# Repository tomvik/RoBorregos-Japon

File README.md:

# RoBorregos-Japon
This repository contains the approach used by RoBorregos Team in the RoboCup 2017 tournament.

RoBorregos is the international representative robotics team of Tecnologico de Monterrey, Campus Monterrey.

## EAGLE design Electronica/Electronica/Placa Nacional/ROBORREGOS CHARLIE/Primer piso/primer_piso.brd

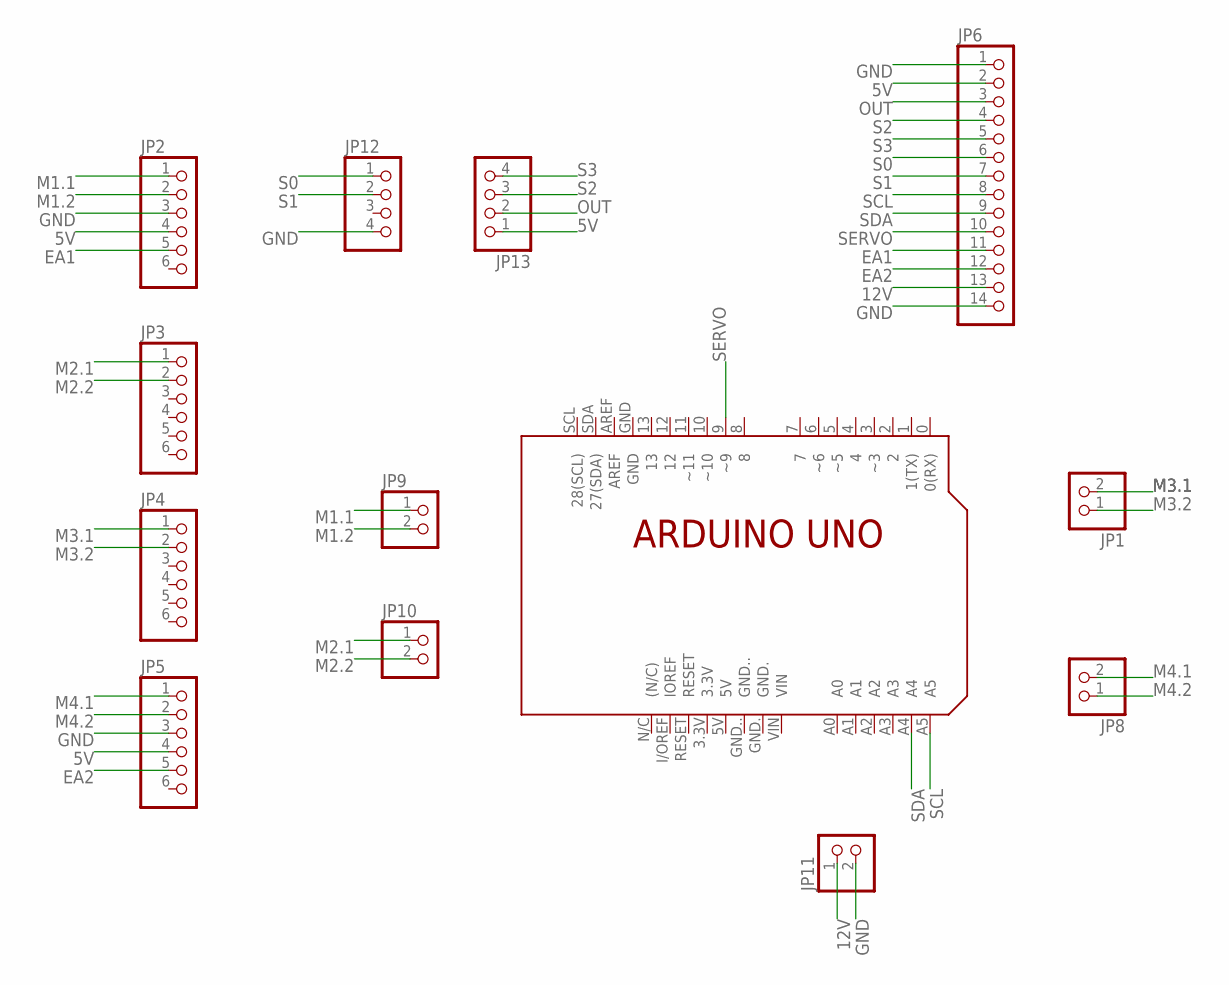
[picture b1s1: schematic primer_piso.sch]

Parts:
JP1, JP8, JP9, JP10, JP11: PINHD-1X2; 1X02
JP2, JP3, JP4, JP5: PINHD-1X6; 1X06
JP6: PINHD-1X14; 1X14
JP12, JP13: PINHD-1X4; 1X04
UNO1: UNO

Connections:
5V: JP2.4, JP5.4, JP6.2, JP13.1
12V: JP6.13, JP11.1
EA1: JP2.5, JP6.11
EA2: JP5.5, JP6.12
GND: JP2.3, JP5.3, JP6.1, JP6.14, JP11.2, JP12.4
M1.1: JP2.1, JP9.1
M1.2: JP2.2, JP9.2
M2.1: JP3.1, JP10.1
M2.2: JP3.2, JP10.2
M3.1: JP1.2, JP4.1
M3.2: JP1.1, JP4.2
M4.1: JP5.1, JP8.2
M4.2: JP5.2, JP8.1
OUT: JP6.3, JP13.2
S0: JP6.6, JP12.1
S1: JP6.7, JP12.2
S2: JP6.4, JP13.3
S3: JP6.5, JP13.4
SCL: JP6.8, UNO1.A5
SDA: JP6.9, UNO1.A4
SERVO: JP6.10, UNO1.9 (~9)

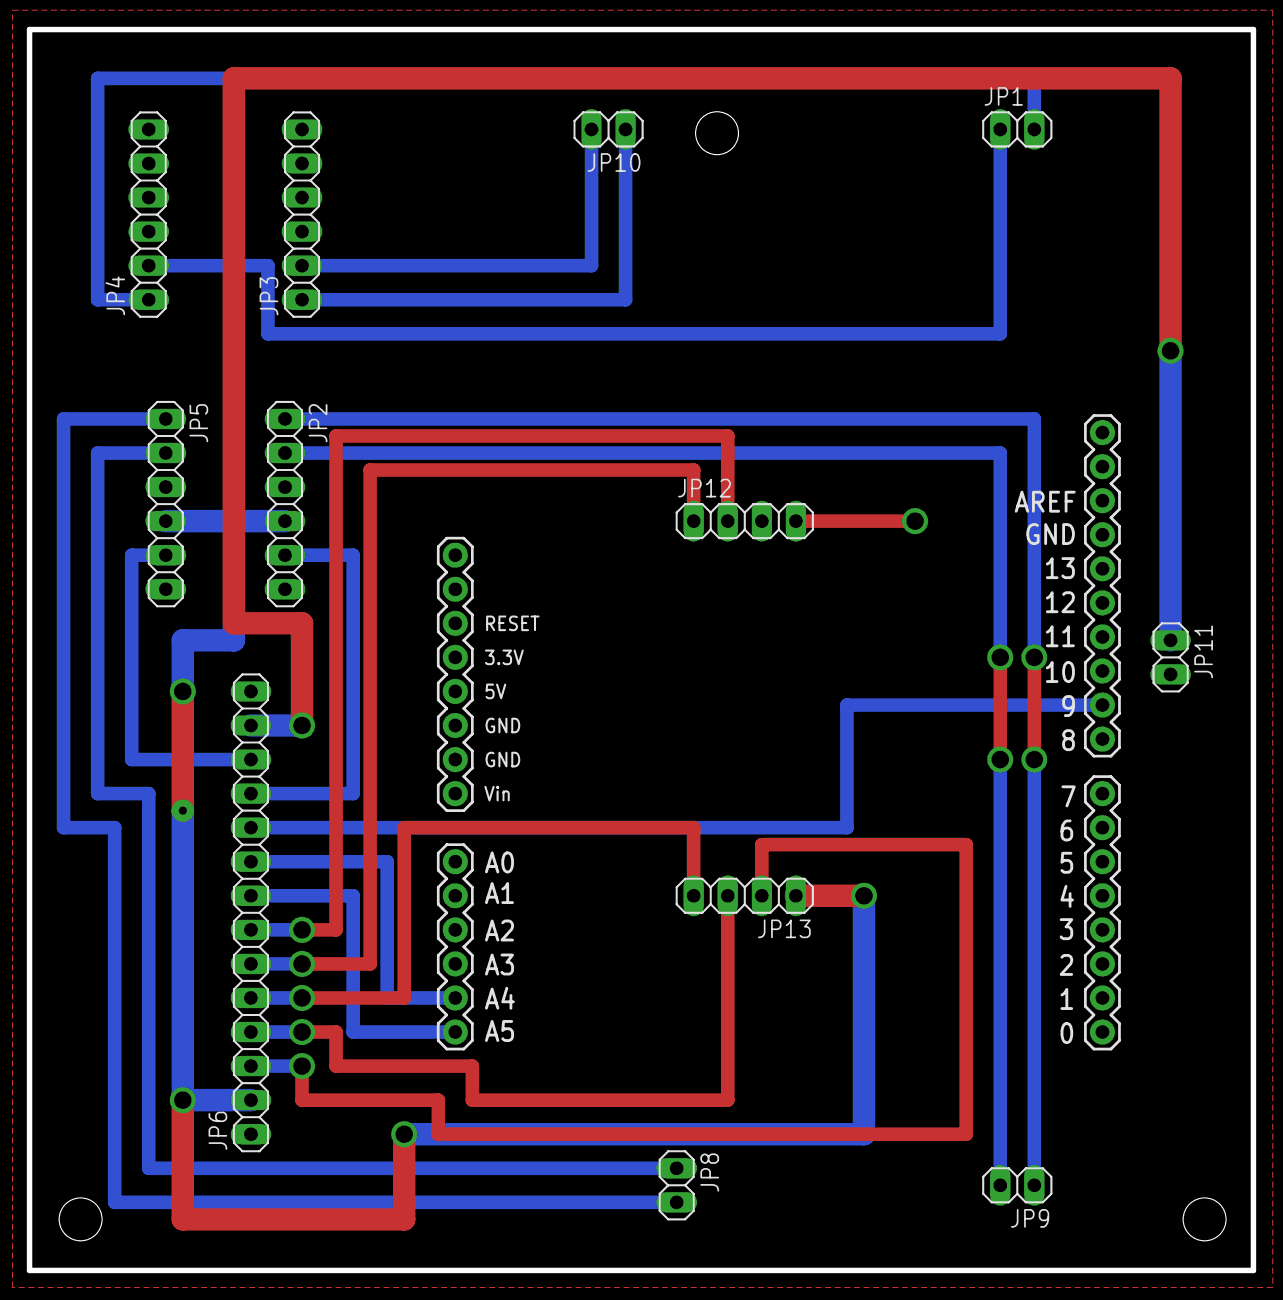
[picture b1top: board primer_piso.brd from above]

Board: 2 copper layers, 91.3 x 92.5 mm, 13 parts (0 on the bottom side), 21 nets.

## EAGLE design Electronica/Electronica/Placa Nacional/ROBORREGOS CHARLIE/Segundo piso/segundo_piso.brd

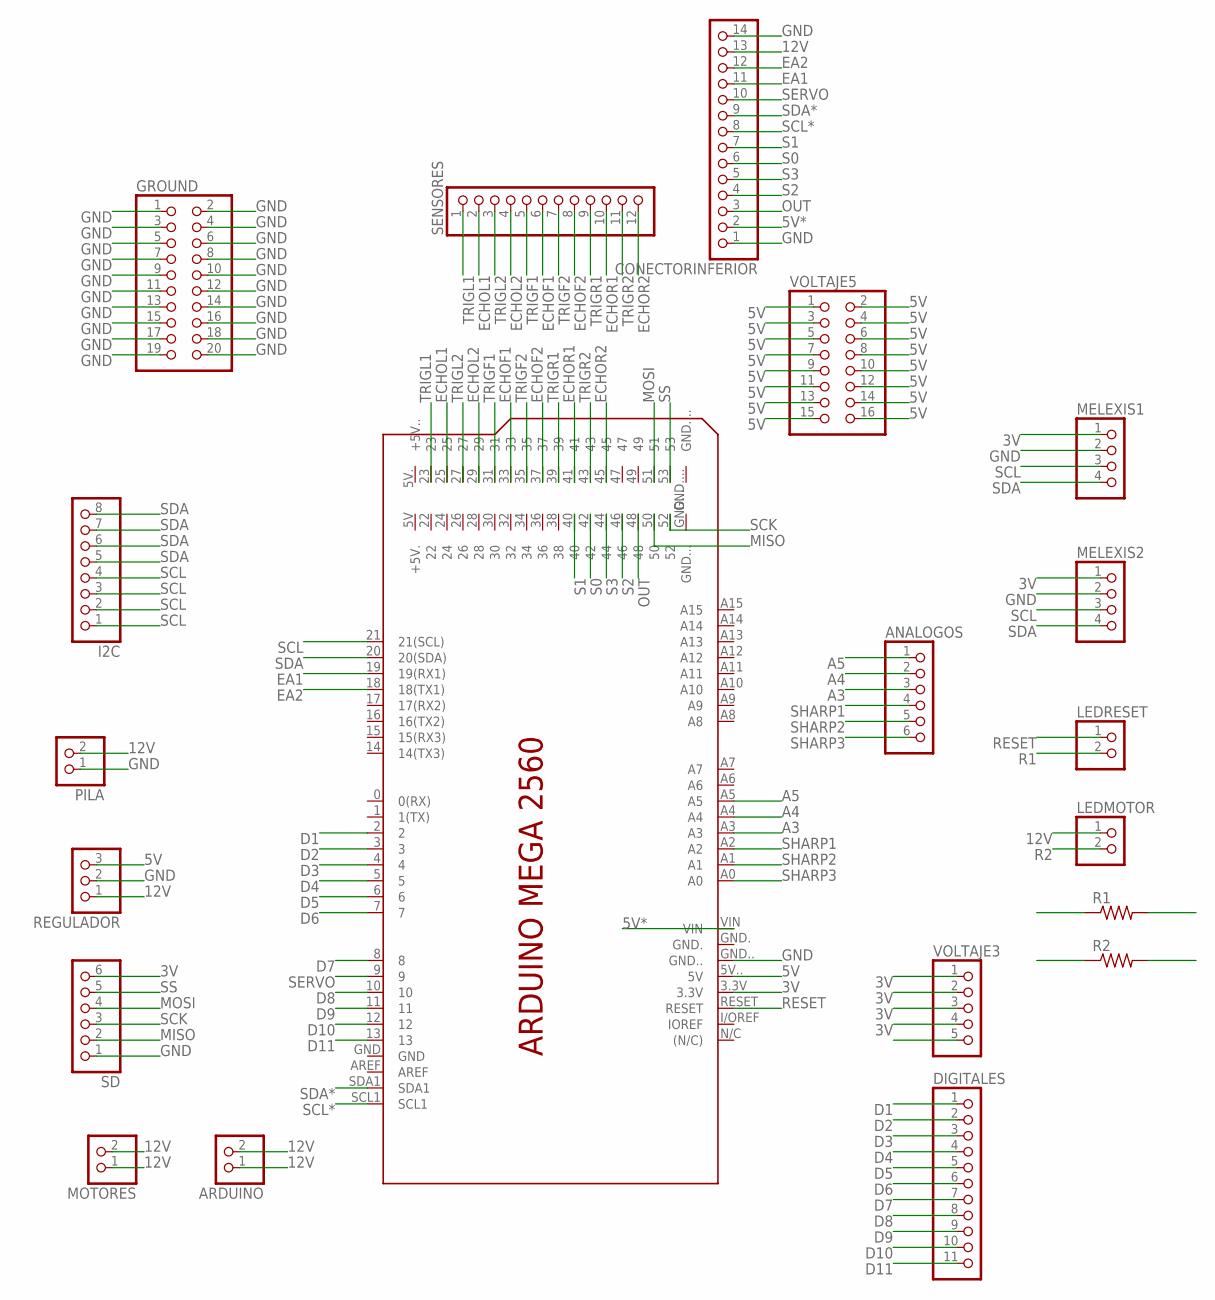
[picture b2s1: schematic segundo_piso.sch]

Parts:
ANALOGOS: PINHD-1X6; 1X06
ARDUINO: PINHD-1X2; 1X02
CONECTORINFERIOR: PINHD-1X14; 1X14
DIGITALES: PINHD-1X11; 1X11
GROUND: PINHD-2X10; 2X10
I2C: PINHD-1X8; 1X08
LEDMOTOR: PINHD-1X2; 1X02
LEDRESET: PINHD-1X2; 1X02
MEGA1: MEGA
MELEXIS1, MELEXIS2: PINHD-1X4; 1X04
MOTORES: PINHD-1X2; 1X02
PILA: PINHD-1X2; 1X02
R1, R2: R-US_0204/7; 0204/7
REGULADOR: PINHD-1X3; 1X03
SD: PINHD-1X6; 1X06
SENSORES: PINHD-1X12; 1X12
VOLTAJE3: PINHD-1X5; 1X05
VOLTAJE5: PINHD-2X8; 2X08

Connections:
3V: MEGA1.3.3V, MELEXIS1.1, MELEXIS2.1, SD.6, VOLTAJE3.1, VOLTAJE3.2, VOLTAJE3.3, VOLTAJE3.4
5V: MEGA1.5V.. (5V), REGULADOR.3, VOLTAJE5.1, VOLTAJE5.2, VOLTAJE5.3, VOLTAJE5.4, VOLTAJE5.5, VOLTAJE5.6, VOLTAJE5.7, VOLTAJE5.8, VOLTAJE5.9, VOLTAJE5.10, VOLTAJE5.11, VOLTAJE5.12, VOLTAJE5.13, VOLTAJE5.14, VOLTAJE5.15, VOLTAJE5.16
5V*: CONECTORINFERIOR.2, MEGA1.VIN
12V: ARDUINO.1, ARDUINO.2, CONECTORINFERIOR.13, LEDMOTOR.1, MOTORES.1, MOTORES.2, PILA.2, REGULADOR.1
A3: ANALOGOS.3, MEGA1.A3
A4: ANALOGOS.2, MEGA1.A4
A5: ANALOGOS.1, MEGA1.A5
D1: DIGITALES.1, MEGA1.2
D2: DIGITALES.2, MEGA1.3
D3: DIGITALES.3, MEGA1.4
D4: DIGITALES.4, MEGA1.5
D5: DIGITALES.5, MEGA1.6
D6: DIGITALES.6, MEGA1.7
D7: DIGITALES.7, MEGA1.8
D8: DIGITALES.8, MEGA1.10
D9: DIGITALES.9, MEGA1.11
D10: DIGITALES.10, MEGA1.12
D11: DIGITALES.11, MEGA1.13
EA1: CONECTORINFERIOR.11, MEGA1.19 (19(RX1))
EA2: CONECTORINFERIOR.12, MEGA1.18 (18(TX1))
ECHOF1: MEGA1.33, SENSORES.6
ECHOF2: MEGA1.37, SENSORES.8
ECHOL1: MEGA1.25, SENSORES.2
ECHOL2: MEGA1.29, SENSORES.4
ECHOR1: MEGA1.41, SENSORES.10
ECHOR2: MEGA1.45, SENSORES.12
GND: CONECTORINFERIOR.1, CONECTORINFERIOR.14, GROUND.1, GROUND.2, GROUND.3, GROUND.4, GROUND.5, GROUND.6, GROUND.7, GROUND.8, GROUND.9, GROUND.10, GROUND.11, GROUND.12, GROUND.13, GROUND.14, GROUND.15, GROUND.16, GROUND.17, GROUND.18, GROUND.19, GROUND.20, MEGA1.GND.., MELEXIS1.2, MELEXIS2.2, PILA.1, R1.2, R2.2, REGULADOR.2, SD.1
MISO: MEGA1.50, SD.2
MOSI: MEGA1.51, SD.4
OUT: CONECTORINFERIOR.3, MEGA1.48
R1: LEDRESET.2, R1.1
R2: LEDMOTOR.2, R2.1
RESET: LEDRESET.1, MEGA1.RESET, VOLTAJE3.5
S0: CONECTORINFERIOR.6, MEGA1.42
S1: CONECTORINFERIOR.7, MEGA1.40
S2: CONECTORINFERIOR.4, MEGA1.46
S3: CONECTORINFERIOR.5, MEGA1.44
SCK: MEGA1.52, SD.3
SCL: I2C.1, I2C.2, I2C.3, I2C.4, MEGA1.21 (21(SCL)), MELEXIS1.3, MELEXIS2.3
SCL*: CONECTORINFERIOR.8, MEGA1.SCL1
SDA: I2C.5, I2C.6, I2C.7, I2C.8, MEGA1.20 (20(SDA)), MELEXIS1.4, MELEXIS2.4
SDA*: CONECTORINFERIOR.9, MEGA1.SDA1
SERVO: CONECTORINFERIOR.10, MEGA1.9
SHARP1: ANALOGOS.4, MEGA1.A2
SHARP2: ANALOGOS.5, MEGA1.A1
SHARP3: ANALOGOS.6, MEGA1.A0
SS: MEGA1.53, SD.5
TRIGF1: MEGA1.31, SENSORES.5
TRIGF2: MEGA1.35, SENSORES.7
TRIGL1: MEGA1.23, SENSORES.1
TRIGL2: MEGA1.27, SENSORES.3
TRIGR1: MEGA1.39, SENSORES.9
TRIGR2: MEGA1.43, SENSORES.11

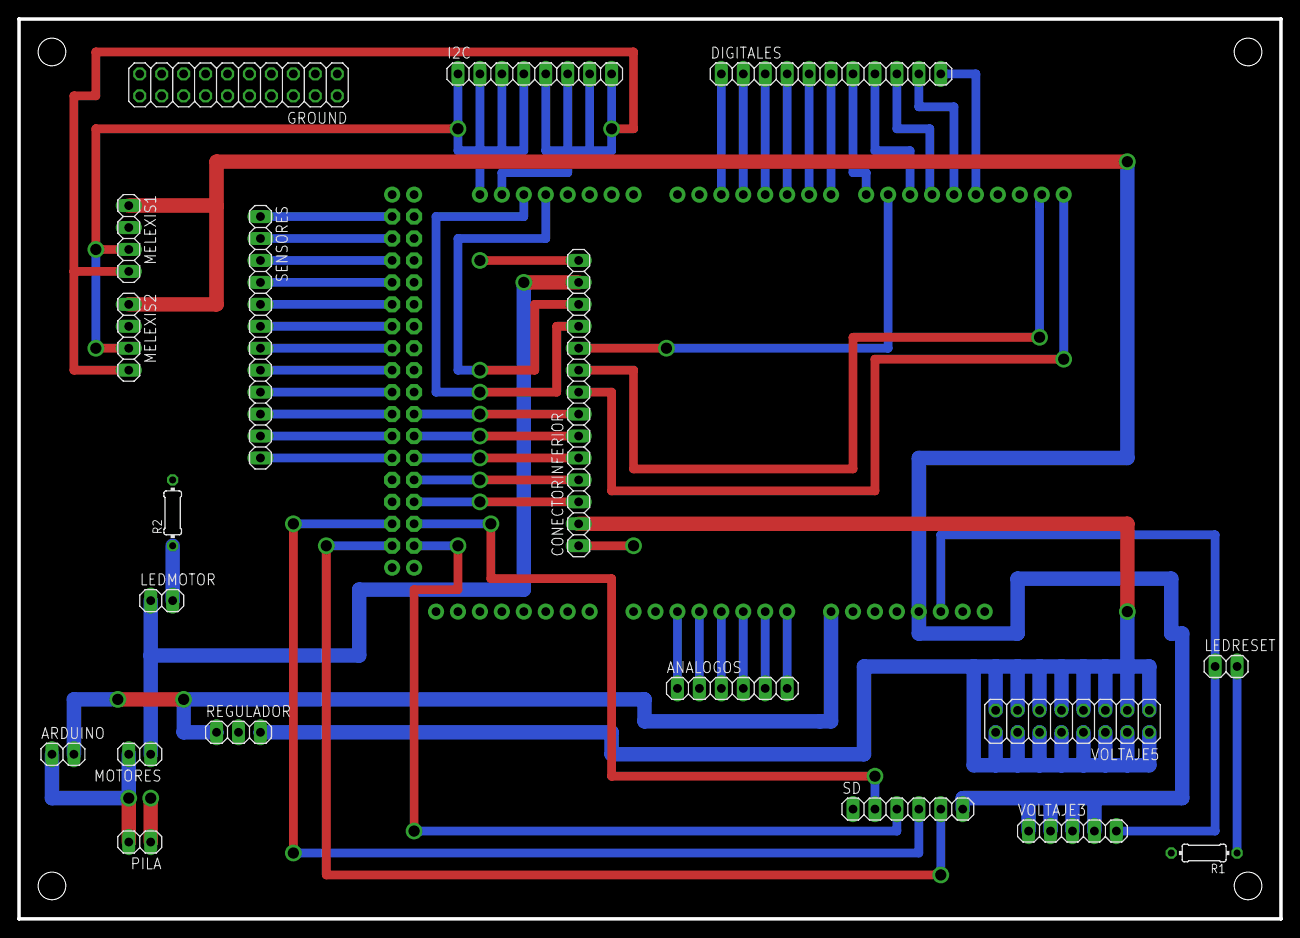
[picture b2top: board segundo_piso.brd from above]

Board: 2 copper layers, 146.1 x 104.1 mm, 20 parts (1 on the bottom side), 53 nets.

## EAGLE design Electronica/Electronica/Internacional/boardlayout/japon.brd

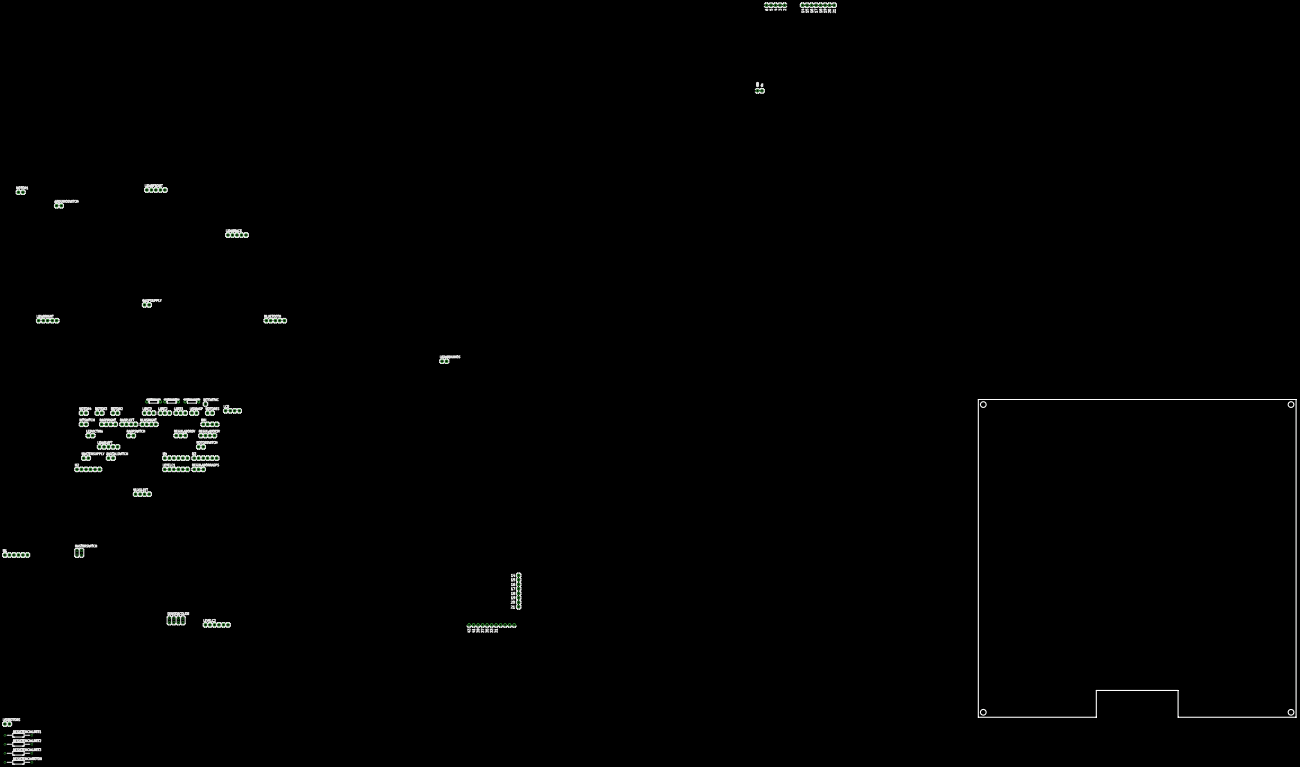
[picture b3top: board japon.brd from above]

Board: 2 copper layers, 179.1 x 179.1 mm, 51 parts (0 on the bottom side), 61 nets, no tracks yet.

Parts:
ARDUINOSWITCH: 1X02
BLUETOOTH: 1X05
DIGITALSWITCH: 1X02
IMU: 1X04
INTSWITCH: 1X02
INTSWITHC: 1X01
LCD: 1X04
LEDARDUINOS: 1X02
LEDMOTORS: 1X02
LEDRASP: 1X02
LEDVICTIMA: 1X02
LEVELC1, LEVELC2: 1X06
LIDARBACK: 1X05
LIDARFRONT: 1X05
LIDARLEFT: 1X05
LIDARRIGHT: 1X05
LIMIT1, LIMIT2, LIMIT3: 1X03
M1, M2, M3, M4: 1X06
MASTERSUPPLY: 1X02
MASTERSWITCH: 2X02
MLXSLEFT: 1X04
MLXSRIGHT: 1X04
MOTOR1, MOTOR2, MOTOR3, MOTOR4: 1X02
MOTORES: 1X02
MOTORSWITCH: 1X02
RASPLEFT: 1X04
RASPRIGHT: 1X04
RASPSUPPLY: 1X02
RASPSWITCH: 1X02
REGULADOR3V: 1X04
REGULADOR5V: 1X03
REGULADORRASPS: 1X03
RESISTENCIAARDUINOS: 1M; AXIAL-0.3
RESISTENCIALIMIT1, RESISTENCIALIMIT2, RESISTENCIALIMIT3: 0207/15
RESISTENCIAMOTOR: 0207/15
RESISTENCIARASPS: 1M; AXIAL-0.3
RESISTENCIAVICTIMAS: 1M; AXIAL-0.3
SENSORCOLOR: 2X04
U$1: MEGASLAVE
U$2: MEGAMASTER

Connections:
3V: IMU.4, LEVELC1.3, LIDARBACK.1, LIDARFRONT.1, LIDARLEFT.1, LIDARRIGHT.1, MLXSLEFT.1, MLXSRIGHT.1, REGULADOR3V.3
5V: DIGITALSWITCH.1, INTSWITCH.1, LCD.1, LEVELC2.4, LIMIT1.3, LIMIT2.3, LIMIT3.3, M1.4, M2.4, REGULADOR5V.3, SENSORCOLOR.8
12V: MASTERSUPPLY.1, MASTERSWITCH.1
12V~: MASTERSWITCH.3, RASPSUPPLY.1
12V~~: ARDUINOSWITCH.1, MASTERSWITCH.2, MOTORSWITCH.1
12V~~~: MASTERSWITCH.4, RASPSWITCH.1
BT: BLUETOOTH.2, U$2.43
DIGSW: DIGITALSWITCH.2, U$2.23
ENCODER1: M1.5, U$2.19
ENCODER2: M2.5, U$2.18
GND: BLUETOOTH.3, IMU.3, LCD.2, LEVELC1.4, LEVELC2.3, LIDARBACK.2, LIDARFRONT.2, LIDARLEFT.2, LIDARRIGHT.2, M1.3, M2.3, M3.3, M4.3, MASTERSUPPLY.2, MLXSLEFT.2, MLXSRIGHT.2, MOTORES.2, RASPLEFT.3, RASPRIGHT.3, RASPSUPPLY.2, REGULADOR3V.2, REGULADOR3V.4, REGULADOR5V.2, REGULADORRASPS.2, RESISTENCIAARDUINOS.P$2, RESISTENCIALIMIT1.2, RESISTENCIALIMIT2.2, RESISTENCIALIMIT3.2, RESISTENCIAMOTOR.2, RESISTENCIARASPS.P$2, RESISTENCIAVICTIMAS.P$2, SENSORCOLOR.7, U$1.GND.
INTSW: INTSWITCH.2, INTSWITHC.1
KEY: BLUETOOTH.1, U$2.41
LIMIT1: LIMIT1.1, U$2.33
LIMIT2: LIMIT2.1, U$2.35
LIMIT3: LIMIT3.1, U$2.37
M1.1: M1.1, MOTOR1.1
M1.2: M1.2, MOTOR1.2
M2.1: M2.1, MOTOR2.1
M2.2: M2.2, MOTOR2.2
M3.1: M3.1, MOTOR3.1
M3.2: M3.2, MOTOR3.2
M4.1: M4.1, MOTOR4.1
M4.2: M4.2, MOTOR4.2
MAIN12: ARDUINOSWITCH.2, LEDARDUINOS.1, REGULADOR3V.1, REGULADOR5V.1, U$1.VIN
MOTOR12: LEDMOTORS.1, MOTORES.1, MOTORSWITCH.2
OUT: SENSORCOLOR.6, U$1.2
R1: LEDARDUINOS.2, RESISTENCIAARDUINOS.P$1
R2: LEDRASP.2, RESISTENCIARASPS.P$1
R3: LEDVICTIMA.2, RESISTENCIAVICTIMAS.P$1
R4: LEDMOTORS.2, RESISTENCIAMOTOR.1
R5: LIMIT1.2, RESISTENCIALIMIT1.1
R6: LIMIT2.2, RESISTENCIALIMIT2.1
R7: LIMIT3.2, RESISTENCIALIMIT3.1
RASPS5: LEDRASP.1, RASPLEFT.4, RASPRIGHT.4, REGULADORRASPS.3
RASPS12: RASPSWITCH.2, REGULADORRASPS.1
RX: U$1.15, U$2.17
RX0: LEVELC2.2, U$1.19
RX0PI: LEVELC1.6, RASPLEFT.2
RX1: LEVELC2.5, U$1.17
RX1PI: LEVELC1.1, RASPRIGHT.2
RX2: BLUETOOTH.4, U$2.15
S0: SENSORCOLOR.1, U$1.3
S1: SENSORCOLOR.3, U$1.4
S2: SENSORCOLOR.4, U$1.5
S3: SENSORCOLOR.2, U$1.6
SCL: IMU.2, LCD.3, LIDARBACK.4, LIDARFRONT.4, LIDARLEFT.4, LIDARRIGHT.4, U$2.21
SCL~: MLXSLEFT.3, MLXSRIGHT.3, U$1.21
SDA: IMU.1, LCD.4, LIDARBACK.3, LIDARFRONT.3, LIDARLEFT.3, LIDARRIGHT.3, U$2.20
SDA~: MLXSLEFT.4, MLXSRIGHT.4, U$1.20
TX: U$1.14, U$2.16
TX0: LEVELC2.1, U$1.18
TX0PI: LEVELC1.5, RASPLEFT.1
TX1: LEVELC2.6, U$1.16
TX1PI: LEVELC1.2, RASPRIGHT.1
TX2: BLUETOOTH.5, U$2.14
VICTIMA: LEDVICTIMA.1, U$2.39
XSHUT1: LIDARFRONT.5, U$2.25
XSHUT2: LIDARRIGHT.5, U$2.27
XSHUT3: LIDARLEFT.5, U$2.29
XSHUT4: LIDARBACK.5, U$2.31

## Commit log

2017-04-24 'Test'
2017-04-29 Rename sketch_nov30a.ino to Algoritmo_Vector1.ino
2017-04-29 Cleans Repository
2017-05-10 Change LibraryCrystal
2017-05-13 Cleaning of functions parameters
2017-05-18 Saves Bumper
2017-05-19 Improvement Go To. Weigthed
2017-05-19 New Control Branch
2017-05-19 Improves Go to function
2017-05-21 Cambios
2017-05-22 Test branch
2017-05-22 Improvement in Path Finding, time and bumper
2017-05-23 Correction of go to error
2017-05-23 Bumper y otras
2017-05-23 Go to final
2017-05-24 LCD everywhere
2017-05-29 Adds puto file
2017-05-30 Tes VL53L0X
2017-06-02 Test VL53L0X
2017-06-02 Improves amount of victims per tile
2017-06-02 Control
2017-06-03 Cleanse Victims
2017-06-04 Improves victim detection
2017-06-04 Limits time Victim
2017-06-05 Cleanse code
2017-06-05 Serial victims
2017-06-05 Improves Serial/Victims/Proccess
2017-06-06 Revert multiple victims
2017-06-06 International mega
2017-06-06 Configurado
2017-06-06 Only one victim/Serial
2017-06-06 Sincronization everything
2017-06-06 Primera
2017-06-06 Folders
2017-06-07 Cambios recientes
2017-06-07 Corrects forward motion
2017-06-14 Nuevo
2017-06-15 Atom
2017-06-17 Versión nueva
2017-06-17 Con ceros
2017-06-17 Ojala
2017-06-18 Limpieza de código y nuevos tests
2017-06-18 Correción en Mapear
2017-06-21 Nuevos test cases, limpieza y cambios de control
2017-06-22 Arreglo en librerias
2017-06-22 Encoder test
2017-06-22 Nuevos test cases y control
2017-06-23 Rename test y IMU
2017-06-23 Version de prueba. CUIDADO.
2017-06-24 IMU changes
2017-06-24 No jala
2017-06-24 Comentar en movimiento
2017-06-24 Revert to f4135be5b3ff2d54e4c8ed66df1c77a3d362dc3d
2017-06-26 Reenommrar
2017-06-26 Nuevos nombres
2017-06-26 Nuevos folders
2017-06-26 Version sin comentar
2017-06-26 Failed
2017-06-27 Encoders, IMU, tests cases, sintaxis
2017-06-28 Sintaxis, control, P e I, vueltas, velocidad, encoder
2017-06-28 Limpieza
2017-06-28 Correciones librerias
2017-06-28 Linrerias
2017-06-28 sintaxis
2017-06-28 Limpieza librerias
2017-06-28 Sintaxis y correciones
2017-06-28 Distancia en milimetros
2017-06-30 Merge
2017-07-01 Correciones y un buen de cosas que si jalan
2017-07-01 Correciones
2017-07-01 Correciones P e I
2017-07-02 Velocidad
2017-07-03 El IMU es una estafa
2017-07-03 Cambios velocidad
2017-07-03 Ojala jale
2017-07-03 main
2017-07-03 Ahora si
2017-07-03 Funcinando
2017-07-04 Corecion front y tiempo inicio
2017-07-04 Tiempo inicial
2017-07-10 Inicio de tests
2017-07-10 Tests
2017-07-10 Correcion limit
2017-07-10 Checkpoint
2017-07-11 Improves Checkpoint
2017-07-11 Cambios limit
2017-07-13 Botones
2017-07-15 Correciones acomoda
2017-07-15 Tiles Arduino
2017-07-15 Falta un caso
2017-07-15 Adds Vision folder and python files
2017-07-15 Final
2017-07-16 Vision
2017-07-17 Improves color and Visual
2017-07-17 Prueba
2017-07-17 Threaded photos
2017-07-18 Cambios push
2017-07-18 bLimit
2017-07-18 Alinearse de lejos
2017-07-18 Super buen avance
2017-07-18 Adds contours
2017-07-19 adds board files
2017-07-19 Cambios de alinearse
2017-07-19 Contadores
2017-07-19 Time limit and resizable map
2017-07-19 rapidez
2017-07-19 Serial
2017-07-19 Cambios control
2017-07-19 YA NO BAILA
2017-07-20 BUG FIX AND SERIAL
2017-07-20 Rampa
2017-07-20 Velocidades muchos bugs y version correcta
2017-07-21 Limit
2017-07-21 Serial and Size
2017-07-22 YA SERIAL JALA
2017-07-23 VERSION FINAL
2017-07-26 ULTIMA
2017-07-26 BUENO
2017-07-27 sdfa
2017-07-27 VERSION FINAL FINAL
2017-07-28 mover
2017-07-28 VERSION SIN CAMBIOS
2017-07-28 VERSION DOS RONDAS BUENAS. CONFIRMADO.
2017-07-28 Con kit en test.
2017-07-28 Pruebas chafas
2017-07-28 Correcion negro
2017-07-28 Negro
2017-07-28 Primera opcion de cambio
2017-07-29 con delays
2017-07-29 YA GANAMOS
2017-12-01 Final comments

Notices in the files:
parts and their libraries:
SparkFun-Resistors: Licensing: Creative Commons ShareAlike 4.0 International - https://creativecommons.org/licenses/by-sa/4.0
